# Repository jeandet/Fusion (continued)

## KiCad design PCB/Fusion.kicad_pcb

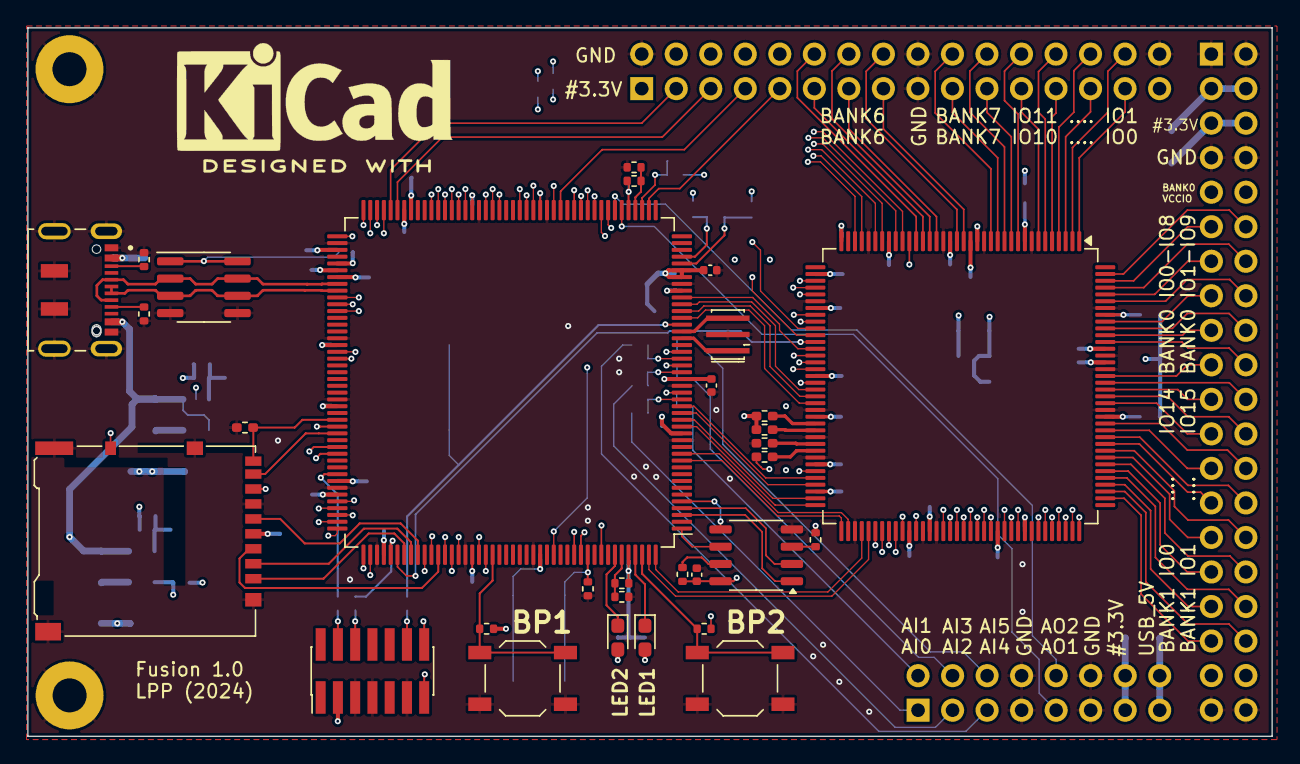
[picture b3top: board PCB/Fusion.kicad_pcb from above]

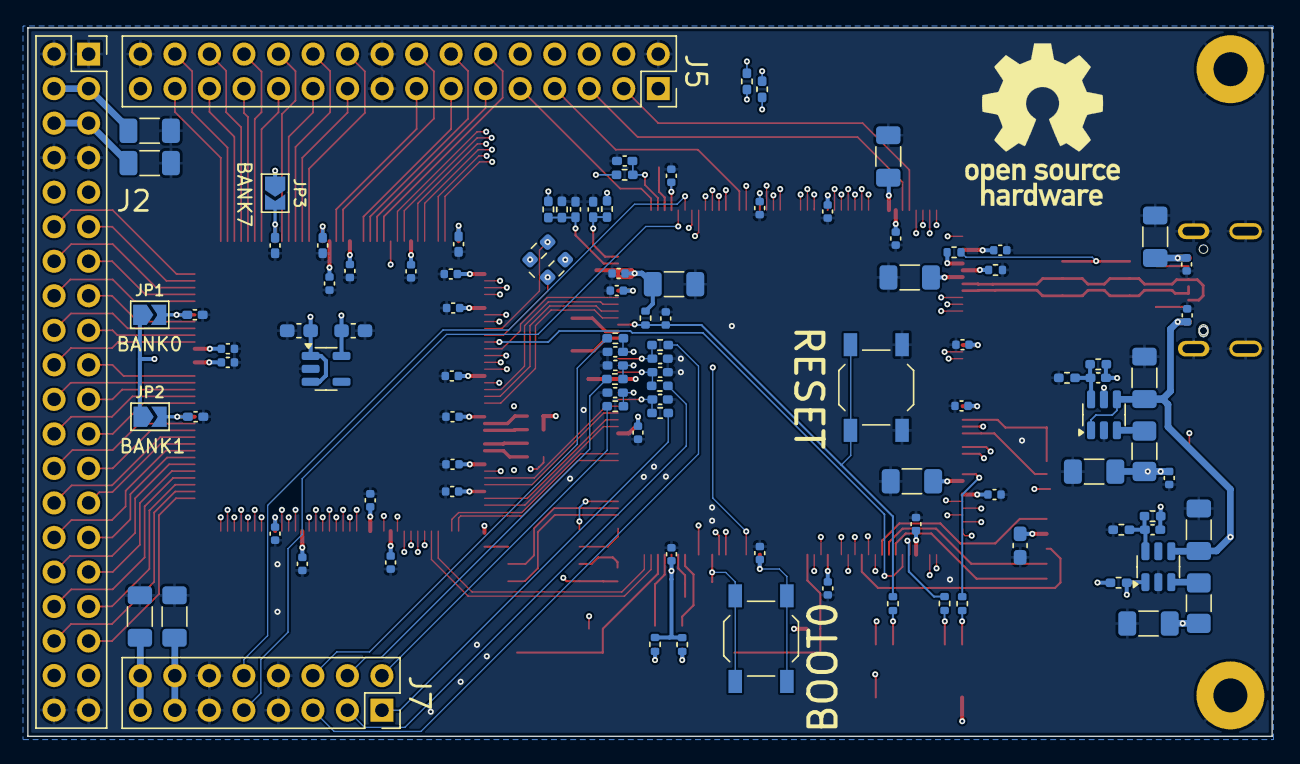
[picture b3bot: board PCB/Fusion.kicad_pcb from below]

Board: 4 copper layers, 91.5 x 52.1 mm, 140 parts (106 on the bottom side), 185 nets.

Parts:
C1: 100nF; C_0603_1608Metric_Pad1.08x0.95mm_HandSolder
C2, C18, C21, C23: 2.2µF; C_1206_3216Metric_Pad1.33x1.80mm_HandSolder
C3, C4, C7, C9, C10, C11, C12, C13, C14, C15, C16, C17, C22, C24, C25, C26, C27, C28, C29, C30, C46, C51, C54, C55, C56, C57, C58, C59, C60, C61, C62, C63, C64, C65, C66, C67, C68: 100nF; C_0402_1005Metric
C5, C31, C33, C35, C36, C47, C48, C69: 100nF; C_0402_1005Metric_Pad0.74x0.62mm_HandSolder
C6, C34, C38, C40: 10uF; C_1206_3216Metric_Pad1.33x1.80mm_HandSolder
C8, C19, C20, C49, C50: 10µF; C_1206_3216Metric_Pad1.33x1.80mm_HandSolder
C32, C39: C; C_0402_1005Metric_Pad0.74x0.62mm_HandSolder
C37, C41, C42, C43, C44, C45: 10nF; C_0402_1005Metric_Pad0.74x0.62mm_HandSolder
C52, C53: 1uF; C_0603_1608Metric_Pad1.08x0.95mm_HandSolder
D1, D2: LED; LED_0603_1608Metric_Pad1.05x0.95mm_HandSolder
H1, H2: MountingHole_Pad; MountingHole_2.5mm_Pad
J1: Micro_SD_Card_Det_Hirose_DM3AT; microSD_HC_Hirose_DM3AT-SF-PEJM5
J2: Conn_02x20_Odd_Even; PinSocket_2x20_P2.54mm_Vertical
J3: DX07S016JA1R1500; JAE_DX07S016JA1R1500
J4: Conn_02x07_Odd_Even; PinHeader_2x07_P1.27mm_Vertical_SMD
J5: Conn_02x16_Odd_Even; PinSocket_2x16_P2.54mm_Vertical
J7: Conn_02x08_Odd_Even; PinSocket_2x08_P2.54mm_Vertical
JP1, JP2, JP3: SolderJumper_2_Open; SolderJumper-2_P1.3mm_Open_TrianglePad1.0x1.5mm
L2, L3: 2.2uH; L_1206_3216Metric_Pad1.42x1.75mm_HandSolder
R1, R2, R3: 22; R_0402_1005Metric
R4, R35, R36, R37, R39, R40, R41: 10k; R_0402_1005Metric_Pad0.72x0.64mm_HandSolder
R5, R6, R7, R8, R9, R14, R16: 100k; R_0402_1005Metric
R10: 3K; R_0402_1005Metric
R11: 820; R_0402_1005Metric
R12, R13, R20, R38: 2.2k; R_0402_1005Metric
R15, R21, R22, R23, R24, R25: 1k; R_0402_1005Metric_Pad0.72x0.64mm_HandSolder
R17, R18: 5.1k; R_0402_1005Metric
R19: 10k; R_0402_1005Metric
R26, R27, R28, R29: 4.7k; R_0402_1005Metric_Pad0.72x0.64mm_HandSolder
R30, R31, R32, R33, R34: R; R_0402_1005Metric_Pad0.72x0.64mm_HandSolder
SW1, SW2: SW_Push; SW_SPST_TL3342
SW3: RESET; SW_SPST_TL3342
SW4: BOOT0; SW_SPST_TL3342
SYM1: Logo_Open_Hardware_Small; OSHW-Logo_11.4x12mm_SilkScreen
SYM2: Logo_Open_Hardware_Small; KiCad-Logo2_8mm_SilkScreen
U1: STM32F723IETx; LQFP-176_24x24mm_P0.5mm
U2, U9: TLV62568DDC; SOT-23-6
U3: MX25L3233FM1; SOP-8_3.9x4.9mm_P1.27mm
U4: LFE5U-12-TG144; TQFP-144_20x20mm_P0.5mm
U5: NCP718xSN250; SOT-23-5
U6: USB6B1; SOIC-8_3.9x4.9mm_P1.27mm
U8: UGA; UGA_0603
Y1: 12MHz; Resonator_SMD_Murata_CSTxExxV-3Pin_3.0x1.1mm_HandSoldering

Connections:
/#1.1V: C39.1, C40.1, C59.1, C60.1, C61.1, C62.1, C63.1, C64.1, L3.2, R30.1, R37.1, U4.20 (VCC[6]), U4.29 (VCC[6]), U4.38 (VCC[6]), U4.66 (VCC[6]), U4.83 (VCC[6]), U4.130 (VCC[6])
/#2.5V: C53.1, C65.1, C66.1, C67.1, C68.1, R41.1, U4.17 (VCCAUX[4]), U4.53 (VCCAUX[4]), U4.96 (VCCAUX[4]), U4.132 (VCCAUX[4]), U5.5 (OUT)
/#3.3V: C1.1, C3.1, C4.1, C7.1, C9.1, C11.1, C12.1, C13.1, C15.1, C16.1, C17.1, C19.1, C22.1, C23.1, C24.1, C25.1, C26.1, C27.1, C28.1, C29.1, C30.1, C32.1, C34.1, C35.1, C36.1, C49.1, C51.1, C52.1, C54.1, C55.1, C56.1, C57.1, C58.1, J1.4 (VDD), J1.10 (DET_A), J2.5, J2.6, J4.3, J5.1, J7.13, J7.14, JP1.1 (A), JP2.1 (A), JP3.1 (A), L2.2, R5.1, R6.1, R8.1, R12.1, R13.1, R14.1, R16.1, R20.2, R26.1, R28.1, R29.1, R31.1, R34.1, R35.1, R38.2, R39.2, R40.2, SW4.1, U1.15 (VDD), U1.23 (VDD), U1.36 (VDD), U1.38 (VREF+), U1.39 (VDDA), U1.49 (VDD), U1.62 (VDD), U1.72 (VDD), U1.82 (VDD), U1.91 (VDD), U1.105 (VDD), U1.114 (VDDUSB), U1.127 (VDD), U1.136 (VDD), U1.149 (VDDSDMMC), U1.159 (VDD), U1.172 (VDD), U3.8 (VCC), U4.16 (VCCIO6[2]), U4.36 (VCCIO6[2]), U4.43 (VCCIO8), U4.59 (CFG_1), U4.70 (VCCIO3[2]), U4.86 (VCCIO3[2]), U4.100 (VCCIO2), U5.1 (IN), U5.3 (EN)
/ADC_IN0: J7.1, R15.1
/ADC_IN1: J7.2, R21.1
/ADC_IN2: J7.3, R22.1
/ADC_IN3: J7.4, R23.1
/ADC_IN4: J7.5, R24.1
/ADC_IN5: J7.6, R25.1
/DAC_OUT1: J7.9, U1.50 (PA4)
/DAC_OUT2: J7.10, U1.51 (PA5)
/FPGA/FPGA_A0: U1.16 (PF0), U4.72 (PR44C/+/RDQ44)
/FPGA/FPGA_A1: U1.17 (PF1), U4.71 (PR47A/+/HS/RDQ44)
/FPGA/FPGA_A2: U1.18 (PF2), U4.69 (PR47C/+/RDQ44/LRC_GPLL0T_IN)
/FPGA/FPGA_BANK0_IO0: J2.19, U4.128 (PT29A/+/PCLKT0_0)
/FPGA/FPGA_BANK0_IO1: J2.20, U4.133 (PT15B/-)
/FPGA/FPGA_BANK0_IO2: J2.17, U4.134 (PT15A/+)
/FPGA/FPGA_BANK0_IO3: J2.18, U4.135 (PT13B/-)
/FPGA/FPGA_BANK0_IO4: J2.15, U4.136 (PT13A/+)
/FPGA/FPGA_BANK0_IO5: J2.16, U4.139 (PT9B/-)
/FPGA/FPGA_BANK0_IO6: J2.13, U4.140 (PT9A/+)
/FPGA/FPGA_BANK0_IO7: J2.14, U4.141 (PT6B/-)
/FPGA/FPGA_BANK0_IO8: J2.11, U4.142 (PT4B/-)
/FPGA/FPGA_BANK0_IO9: J2.12, U4.143 (PT6A/+)
/FPGA/FPGA_BANK1_IO0: J2.35, U4.110 (PT67A/+)
/FPGA/FPGA_BANK1_IO1: J2.36, U4.111 (PT62B/-)
/FPGA/FPGA_BANK1_IO2: J2.33, U4.112 (PT62A/+)
/FPGA/FPGA_BANK1_IO3: J2.34, U4.113 (PT60B/-)
/FPGA/FPGA_BANK1_IO4: J2.31, U4.114 (PT60A/+)
/FPGA/FPGA_BANK1_IO5: J2.32, U4.115 (PT58B/-)
/FPGA/FPGA_BANK1_IO6: J2.29, U4.116 (PT58A/+)
/FPGA/FPGA_BANK1_IO7: J2.30, U4.117 (PT56B/-)
/FPGA/FPGA_BANK1_IO8: J2.27, U4.118 (PT56A/+)
/FPGA/FPGA_BANK1_IO9: J2.28, U4.119 (PT53B/-)
/FPGA/FPGA_BANK1_IO10: J2.25, U4.120 (PT53A/+)
/FPGA/FPGA_BANK1_IO11: J2.26, U4.121 (PT51A/+)
/FPGA/FPGA_BANK1_IO12: J2.23, U4.124 (PT42B/-)
/FPGA/FPGA_BANK1_IO13: J2.24, U4.125 (PT42A/+)
/FPGA/FPGA_BANK1_IO14: J2.21, U4.126 (PT40B/-)
/FPGA/FPGA_BANK1_IO15: J2.22, U4.127 (PT40A/+)
/FPGA/FPGA_BANK6_IO0: J5.15, U4.18 (PL32B/-/HS/LDQSN32)
/FPGA/FPGA_BANK6_IO1: J5.16, U4.19 (PL35B/-/HS/LDQ32/VREF1_6)
/FPGA/FPGA_BANK6_IO2: J5.13, U4.22 (PL35C/+/LDQ32)
/FPGA/FPGA_BANK6_IO3: J5.14, U4.23 (PL35D/-/LDQ32)
/FPGA/FPGA_BANK6_IO4: J5.11, U4.24 (PL38A/+/HS/LDQ44)
/FPGA/FPGA_BANK6_IO5: J5.12, U4.25 (PL38B/-/HS/LDQ44)
/FPGA/FPGA_BANK7_IO0: J5.29, U4.1 (PL5C/+/LDQ8)
/FPGA/FPGA_BANK7_IO1: J5.30, U4.2 (PL5D/-/LDQ8)
/FPGA/FPGA_BANK7_IO2: J5.27, U4.3 (PL5B/-/HS/LDQ8)
/FPGA/FPGA_BANK7_IO3: J5.28, U4.4 (PL8A/+/HS/LDQS8)
/FPGA/FPGA_BANK7_IO4: J5.25, U4.5 (PL8C/+/LDQ8)
/FPGA/FPGA_BANK7_IO5: J5.26, U4.6 (PL8B/-/HS/LDQSN8)
/FPGA/FPGA_BANK7_IO6: J5.23, U4.7 (PL8D/-/LDQ8)
/FPGA/FPGA_BANK7_IO7: J5.24, U4.10 (PL14A/+/HS/LDQ20)
/FPGA/FPGA_BANK7_IO8: J5.21, U4.11 (PL14C/+/LDQ20/VREF1_7)
/FPGA/FPGA_BANK7_IO9: J5.22, U4.12 (PL14B/-/HS/LDQ20)
/FPGA/FPGA_BANK7_IO10: J5.19, U4.13 (PL14D/-/LDQ20)
/FPGA/FPGA_BANK7_IO11: J5.20, U4.14 (PL23D/-/LDQ20/PCLKC7_0)
/FPGA/FPGA_CFG_CLK: U1.161 (PB3), U4.54 (CCLK/MCLK/SCK)
/FPGA/FPGA_CFG_CS: U1.138 (PA15), U4.48 (PB13A/+/SN/CSN)
/FPGA/FPGA_CFG_DONE: U1.33 (PC1), U4.56 (DONE)
/FPGA/FPGA_CFG_HOLDN: U1.35 (PC3), U4.49 (PB15A/+/HOLDN/DI/BUSY/CSSPIN/CEN)
/FPGA/FPGA_CFG_INIT: U1.34 (PC2), U4.55 (INITN)
/FPGA/FPGA_CFG_MISO: U1.52 (PA6), U8.1 (RX1)
/FPGA/FPGA_CFG_MOSI: U1.53 (PA7), U8.2 (TX1)
/FPGA/FPGA_CFG_PROGRAMN: U1.32 (PC0), U4.57 (PROGRAMN)
/FPGA/FPGA_CLK: U1.145 (PD3), U4.93 (PR20B/-/HS/RDQSN20)
/FPGA/FPGA_D0: U1.106 (PD14), U4.97 (PR14B/-/HS/RDQ20)
/FPGA/FPGA_D1: U1.107 (PD15), U4.95 (PR20A/+/HS/RDQS20/GR_PCLK2_1)
/FPGA/FPGA_D2: U1.142 (PD0), U4.91 (PR23A/+/HS/RDQ20/PCLKT2_1)
/FPGA/FPGA_D3: U1.143 (PD1), U4.92 (PR20D/-/RDQ20)
/FPGA/FPGA_D4: U1.68 (PE7), U4.39 (PB6A/+/D5/MISO2/IO5)
/FPGA/FPGA_D5: U1.69 (PE8), U4.40 (PB4A/+/D7/IO7)
/FPGA/FPGA_D6: U1.70 (PE9), U4.41 (PB6B/-/D4/MOSI2/IO4)
/FPGA/FPGA_D7: U1.73 (PE10), U4.44 (PB4B/-/D6/IO6)
/FPGA/FPGA_D8: U1.74 (PE11), U4.45 (PB9A/+/D3/IO3)
/FPGA/FPGA_D9: U1.75 (PE12), U4.50 (PB13B/-/CS1N)
/FPGA/FPGA_D10: U1.76 (PE13), U4.51 (PB15B/-/DOUT/CSON)
/FPGA/FPGA_D11: U1.77 (PE14), U4.52 (PB18A/WRITEN)
/FPGA/FPGA_D12: U1.78 (PE15), U4.108 (PR2B/-/HS/RDQ8/S0_IN)
/FPGA/FPGA_D13: U1.98 (PD8), U4.102 (PR8D/-/RDQ8)
/FPGA/FPGA_D14: U1.99 (PD9), U4.99 (PR14A/+/HS/RDQ20)
/FPGA/FPGA_D15: U1.100 (PD10), U4.98 (PR14C/+/RDQ20/VREF1_2)
/FPGA/FPGA_D16: U1.85 (PH8), U4.107 (PR2C/+/RDQ8)
/FPGA/FPGA_D17: U1.86 (PH9), U4.106 (PR2D/-/RDQ8)
/FPGA/FPGA_D18: U1.87 (PH10), U4.105 (PR8A/+/HS/RDQS8)
/FPGA/FPGA_D19: U1.88 (PH11), U4.104 (PR8C/+/RDQ8)
/FPGA/FPGA_D20: U1.89 (PH12), U4.103 (PR8B/-/HS/RDQSN8)
/FPGA/FPGA_D21: U1.128 (PH13), U4.88 (PR23D/-/RDQ20/PCLKC2_0)
/FPGA/FPGA_D22: U1.129 (PH14), U4.84 (PR32C/+/RDQ32)
/FPGA/FPGA_D23: U1.130 (PH15), U4.82 (PR32D/-/RDQ32)
/FPGA/FPGA_D24: U1.131 (PI0), U4.81 (PR35A/+/HS/RDQ32)
/FPGA/FPGA_D25: U1.132 (PI1), U4.80 (PR35C/+/RDQ32)
/FPGA/FPGA_D26: U1.133 (PI2), U4.78 (PR35D/-/RDQ32)
/FPGA/FPGA_D27: U1.134 (PI3), U4.79 (PR35B/-/HS/RDQ32/VREF1_3)
/FPGA/FPGA_D28: U1.175 (PI6), U4.77 (PR41A/+/HS/RDQ44)
/FPGA/FPGA_D29: U1.176 (PI7), U4.76 (PR41B/-/HS/RDQ44)
/FPGA/FPGA_D30: U1.11 (PI9), U4.73 (PR41D/-/RDQ44)
/FPGA/FPGA_D31: U1.12 (PI10), U4.74 (PR41C/+/RDQ44)
/FPGA/FPGA_HAVE_DATA: U1.19 (PF3), U4.68 (PR47D/-/RDQ44/LRC_GPLL0C_IN)
/FPGA/FPGA_IO0: U1.54 (PC4), U4.34 (PL47A/+/HS/LDQ44)
/FPGA/FPGA_IO1: U1.55 (PC5), U4.33 (PL44D/-/LDQ44)
/FPGA/FPGA_IO2: U1.60 (PF12), U4.31 (PL44C/+/LDQ44)
/FPGA/FPGA_IO3: U1.63 (PF13), U4.30 (PL44B/-/HS/LDQSN44)
/FPGA/FPGA_IO4: U1.64 (PF14), U4.28 (PL44A/+/HS/LDQS44)
/FPGA/FPGA_IO5: U1.65 (PF15), U4.27 (PL41D/-/LDQ44)
/FPGA/FPGA_NE1: U1.151 (PD7), U4.89 (PR23B/-/HS/RDQ20/PCLKC2_1)
/FPGA/FPGA_NL: U1.165 (PB7), U4.26 (PL41C/+/LDQ44)
/FPGA/FPGA_NOE: U1.146 (PD4), U4.90 (PR23C/+/RDQ20/PCLKT2_0)
/FPGA/FPGA_NWAIT: U1.150 (PD6), U4.67 (PR47B/-/HS/RDQ44)
/FPGA/FPGA_NWE: U1.147 (PD5), U4.94 (PR20C/+/RDQ20/GR_PCLK2_0)
/FPGA_BANK0_VCCIO: C31.1, J2.9, J2.10, JP1.2 (B), U4.137 (VCCIO0)
/FPGA_BANK1_VCCIO: C5.1, J2.37, J2.38, JP2.2 (B), U4.122 (VCCIO1)
/FPGA_BANK7_VCCIO: C33.1, J5.31, JP3.2 (B), U4.9 (VCCIO7)
/I2C1_SCL: J5.6, R40.1, U1.164 (PB6)
/I2C1_SDA: J5.4, R39.1, U1.168 (PB9)
/MCU/ADC_HK_1.1V: C48.1, R37.2, U1.41 (PA1)
/MCU/ADC_HK_2.5V: C69.1, R41.2, U1.47 (PA3)
/MCU/ADC_HK_3.3V: C47.1, R35.2, R36.2, U1.40 (PA0)
/MCU/BOOT0: R9.1, SW4.2, U1.166 (BOOT0)
/MCU/BYPASS_REG: R5.2, R19.1, U1.48 (BYPASS_REG)
/MCU/CARD_DETECT: J1.9 (DET_B), R4.2, U1.116 (PC7)
/MCU/LED1: D1.1 (K), U1.173 (PI4)
/MCU/LED2: D2.1 (K), U1.170 (PE1)
/MCU/PDR_ON: R6.2, R7.1, U1.171 (PDR_ON)
/MCU/RESET: C14.1, R3.2, R8.2, SW3.1, U1.31 (NRST)
/MCU/SDMMC_CLK: J1.5 (CLK), U1.141 (PC12)
/MCU/SDMMC_CMD: J1.3 (CMD), U1.144 (PD2)
/MCU/SDMMC_D0: J1.7 (DAT0), U1.117 (PC8)
/MCU/SDMMC_D1: J1.8 (DAT1), U1.118 (PC9)
/MCU/SDMMC_D2: J1.1 (DAT2), U1.139 (PC10)
/MCU/SDMMC_D3: J1.2 (DAT3/CD), U1.140 (PC11)
/MCU/SPI_FLASH_CS: U1.3 (PE4), U3.1 (~CS)
/MCU/SPI_FLASH_MISO: U1.4 (PE5), U3.2 (SO/SIO1)
/MCU/SPI_FLASH_MOSI: U1.5 (PE6), U3.5 (SI/SIO0)
/MCU/SPI_FLASH_SCK: U1.1 (PE2), U3.6 (SCLK)
/MCU/SWCLK: R2.2, U1.137 (PA14)
/MCU/SWDIO: R1.2, U1.124 (PA13)
/MCU/USB_D+: J3.6 (D+), J3.7 (D+), U1.97 (PB15), U6.3 (I/O2), U6.6 (I/O2)
/MCU/USB_D-: J3.5 (D-), J3.8 (D-), U1.96 (PB14), U6.2 (I/O1), U6.7 (I/O1)
/MCU/USER_BP1: R16.2, SW1.1, U1.152 (PG9)
/MCU/USER_BP2: R14.2, SW2.1, U1.174 (PI5)
/MCU/VCP_RX: J4.13, U1.121 (PA10)
/MCU/VCP_TX: J4.14, U1.120 (PA9)
/MCU/_ADC_IN0: C37.1, R15.2, U1.20 (PF4)
/MCU/_ADC_IN1: C41.1, R21.2, U1.21 (PF5)
/MCU/_ADC_IN2: C42.1, R22.2, U1.24 (PF6)
/MCU/_ADC_IN3: C43.1, R23.2, U1.25 (PF7)
/MCU/_ADC_IN4: C44.1, R24.2, U1.26 (PF8)
/MCU/_ADC_IN5: C45.1, R25.2, U1.27 (PF9)
/Power/TLV62568/PG: R34.2, U2.5 (PG), U9.1 (EN)
/SPI5_MISO: J5.3, U1.84 (PH7)
/SPI5_MOSI: J5.7, U1.59 (PF11)
/SPI5_NSS: J5.9, U1.46 (PH5)
/SPI5_SCK: J5.5, U1.83 (PH6)
/UC_GPIO0: J5.10, U1.56 (PB0)
/UC_GPIO1: J5.8, U1.57 (PB1)
/USB_5V: C6.1, C8.1, C10.1, C20.1, C38.1, C46.1, C50.1, J2.3, J2.4, J3.2 (VBUS), J3.11 (VBUS), J7.15, J7.16, R11.2, U2.1 (EN), U2.4 (VIN), U6.1 (VBUS), U6.8 (VBUS), U9.4 (VIN)
GND: C1.2, C2.2, C3.2, C4.2, C5.2, C6.2, C7.2, C8.2, C9.2, C10.2, C11.2, C12.2, C13.2, C14.2, C15.2, C16.2, C17.2, C18.2, C19.2, C20.2, C21.2, C22.2, C23.2, C24.2, C25.2, C26.2, C27.2, C28.2, C29.2, C30.2, C31.2, C33.2, C34.2, C35.2, C36.2, C37.2, C38.2, C40.2, C41.2, C42.2, C43.2, C44.2, C45.2, C46.2, C47.2, C48.2, C49.2, C50.2, C51.2, C52.2, C53.2, C54.2, C55.2, C56.2, C57.2, C58.2, C59.2, C60.2, C61.2, C62.2, C63.2, C64.2, C65.2, C66.2, C67.2, C68.2, C69.2, H1.1, H2.1, J1.6 (VSS), J1.11 (SHIELD), J2.1, J2.2, J2.7, J2.8, J2.39, J2.40, J3.1 (GND), J3.12 (GND), J3.S1 (SHIELD), J3.S2 (SHIELD), J3.S3 (SHIELD), J3.S4 (SHIELD), J3.S5 (SHIELD), J3.S6 (SHIELD), J4.5, J4.7, J4.11, J5.2, J5.17, J5.18, J5.32, J7.7, J7.8, J7.11, J7.12, R4.1, R7.2, R9.2, R10.2, R17.1, R18.1, R19.2, R27.1, R32.2, R33.2, R36.1, SW1.2, SW2.2, SW3.2, U1.14 (VSS), U1.22 (VSS), U1.37 (VSSA), U1.61 (VSS), U1.71 (VSS), U1.90 (VSS), U1.104 (VSS), U1.113 (VSS), U1.126 (VSS), U1.135 (VSS), U1.148 (VSS), U1.158 (VSS), U2.2 (GND), U3.4 (GND), U4.8 (GND[13]), U4.15 (GND[13]), U4.21 (GND[13]), U4.32 (VSSIO6), U4.42 (GND[13]), U4.58 (CFG_2), U4.62 (CFG_0), U4.65 (GND[13]), U4.75 (GND[13]), U4.85 (GND[13]), U4.87 (GND[13]), U4.101 (GND[13]), U4.123 (GND[13]), U4.129 (GND[13]), U4.131 (GND[13]), U4.138 (GND[13]), U5.2 (GND), U6.4 (GND), U6.5 (GND), U9.2 (GND), Y1.2
unnamed: D1.2 (A), R12.2
unnamed: D2.2 (A), R13.2
unnamed: J3.3 (CC1), R17.2
unnamed: J3.9 (CC2), R18.2
unnamed: J4.4, R1.1
unnamed: J4.6, R2.1
unnamed: J4.12, R3.1
unnamed: R11.1, U1.93 (PB13)
unnamed: U1.29 (PH0), Y1.1
unnamed: U1.30 (PH1), Y1.3
unnamed: R10.1, U1.94 (REXTPHYHS)
unnamed: C18.1, U1.95 (V12PHYHS)
unnamed: C21.1, U1.81 (VCAP_1)
unnamed: C2.1, U1.125 (VCAP_2)
unnamed: C32.2, R31.2, R32.1, U2.6 (FB)
unnamed: L2.1, U2.3 (SW)
unnamed: R38.1, U3.7 (~HOLD/SIO3)
unnamed: R20.1, U3.3 (~WP/SIO2)
unnamed: U4.46 (PB11A/+/D1/MISO/IO1), U8.4 (TX2)
unnamed: U4.47 (PB11B/-/D0/MOSI/IO0), U8.3 (RX2)
unnamed: R27.2, U4.63 (TCK)
unnamed: R28.2, U4.61 (TDI)
unnamed: R26.2, U4.60 (TDO)
unnamed: R29.2, U4.64 (TMS)
unnamed: C39.2, R30.2, R33.1, U9.6 (FB)
unnamed: L3.1, U9.3 (SW)

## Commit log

2024-03-04 initial layout
2024-03-15 release 1.0 ready for production
2024-03-25 AnaloghTwo ready for review
2024-03-28 AnaloghTwo ready for production
2024-04-10 Some last minute fixes
2024-08-24 Fixes mistake in 1.0, FPGA boot cgf was forced into Master SPI mode
    Just make it configurable with pull down resistors.
2024-08-26 Fixes FPGA CFG slave serial interface wiring
2025-05-30 New Fusion main board version using a more beefy MCU.
2025-07-20 New FPGA only version
